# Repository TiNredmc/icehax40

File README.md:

# iCEHAX40
iCEHAX40 - iCE40LP1K-CM36 based FPGA breakout dev board https://oshpark.com/shared_projects/n9XXjf2W

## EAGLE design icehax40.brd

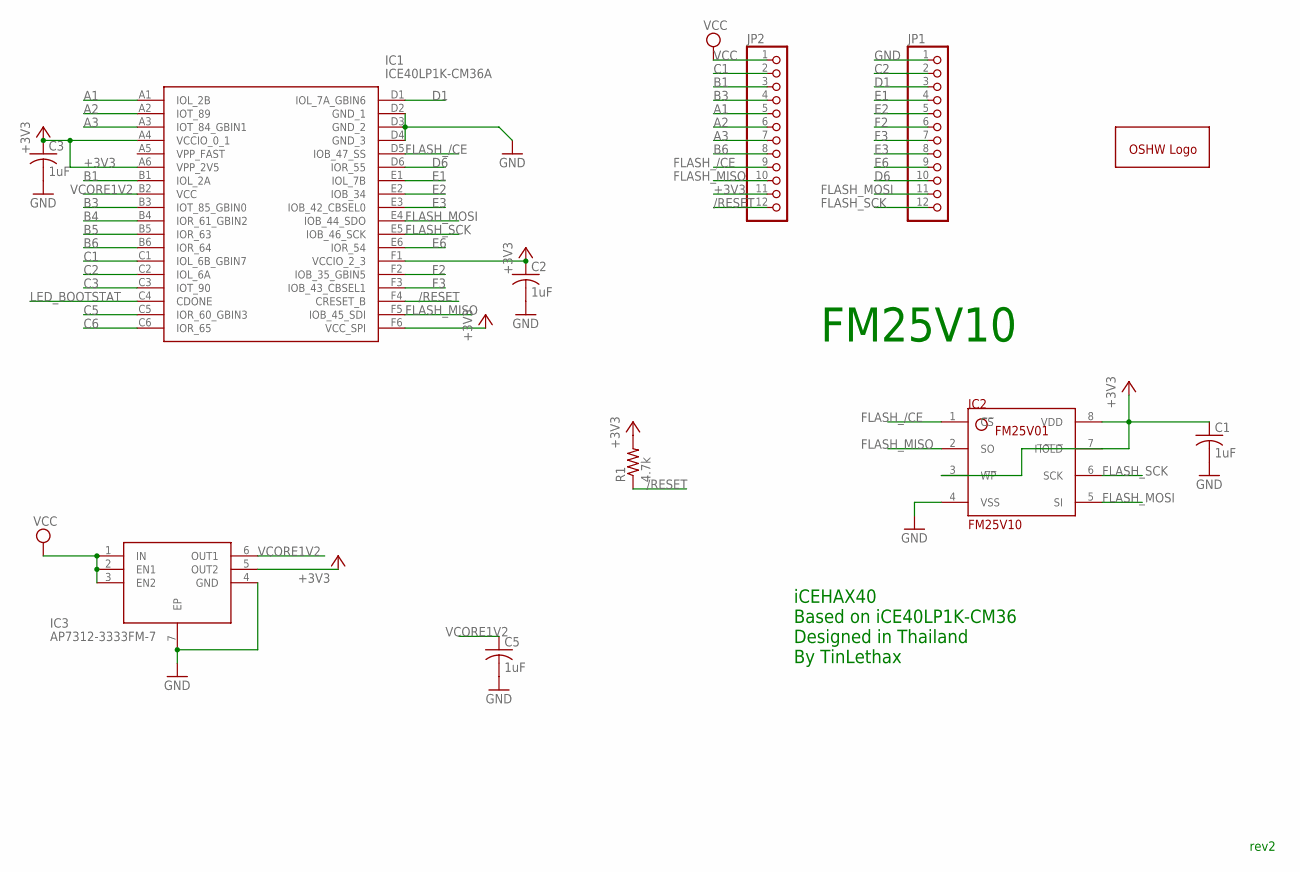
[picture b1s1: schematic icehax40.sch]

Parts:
C1, C2, C3, C5: 1uF; C0603
GOLD_ORB_SM1: OSHWLOGOLOGO5MM; OSHW_5MM
IC1: ICE40LP1K-CM36A; BGA36C40P6X6_250X250X100
IC2: FM25V10; SOIC127P601X172-8N
IC3: AP7312-3333FM-7; SON50P201X181X60-7N
JP1, JP2: PINHD-1X12; 1X12
R1: 4.7k; R0603

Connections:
+3V3: C1.1, C2.1, C3.1, IC1.A4 (VCCIO_0_1), IC1.A6 (VPP_2V5), IC1.F1 (VCCIO_2_3), IC1.F6 (VCC_SPI), IC2.3 (W̅P̅), IC2.7 (H̅O̅L̅D̅), IC2.8 (VDD), IC3.5 (OUT2), JP2.11, R1.2
/RESET: IC1.F4 (CRESET_B), JP2.12, R1.1
A1: IC1.A1 (IOL_2B), JP2.5
A2: IC1.A2 (IOT_89), JP2.6
A3: IC1.A3 (IOT_84_GBIN1), JP2.7
B1: IC1.B1 (IOL_2A), JP2.3
B3: IC1.B3 (IOT_85_GBIN0), JP2.4
B4: IC1.B4 (IOR_61_GBIN2)
B5: IC1.B5 (IOR_63)
B6: IC1.B6 (IOR_64), JP2.8
C1: IC1.C1 (IOL_6B_GBIN7), JP2.2
C2: IC1.C2 (IOL_6A), JP1.2
C3: IC1.C3 (IOT_90)
C5: IC1.C5 (IOR_60_GBIN3)
C6: IC1.C6 (IOR_65)
D1: IC1.D1 (IOL_7A_GBIN6), JP1.3
D6: IC1.D6 (IOR_55), JP1.10
E1: IC1.E1 (IOL_7B), JP1.4
E2: IC1.E2 (IOB_34), JP1.5
E3: IC1.E3 (IOB_42_CBSEL0), JP1.8
E6: IC1.E6 (IOR_54), JP1.9
F2: IC1.F2 (IOB_35_GBIN5), JP1.6
F3: IC1.F3 (IOB_43_CBSEL1), JP1.7
FLASH_/CE: IC1.D5 (IOB_47_SS), IC2.1 (C̅S̅), JP2.9
FLASH_MISO: IC1.F5 (IOB_45_SDI), IC2.2 (SO), JP2.10
FLASH_MOSI: IC1.E4 (IOB_44_SDO), IC2.5 (SI), JP1.11
FLASH_SCK: IC1.E5 (IOB_46_SCK), IC2.6 (SCK), JP1.12
GND: C1.2, C2.2, C3.2, C5.2, IC1.D2 (GND_1), IC1.D3 (GND_2), IC1.D4 (GND_3), IC2.4 (VSS), IC3.4 (GND), IC3.7 (EP), JP1.1
LED_BOOTSTAT: IC1.C4 (CDONE)
VCC: IC3.1 (IN), IC3.2 (EN1), IC3.3 (EN2), JP2.1
VCORE1V2: C5.1, IC1.B2 (VCC), IC3.6 (OUT1)

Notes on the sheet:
iCEHAX40 Based on iCE40LP1K-CM36 Designed in Thailand By TinLethax
FM25V10
rev2

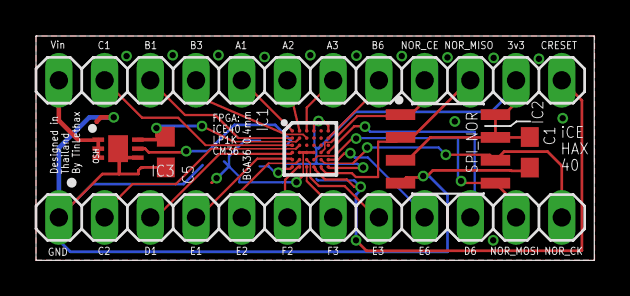
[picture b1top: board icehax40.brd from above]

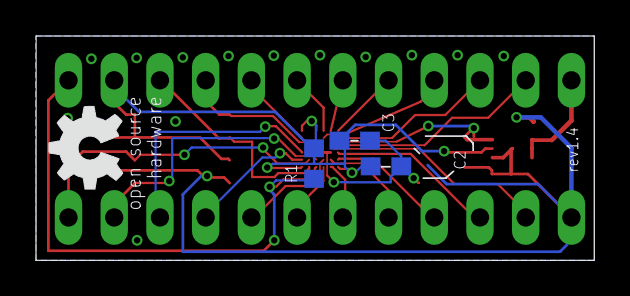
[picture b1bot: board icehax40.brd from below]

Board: 2 copper layers, 31.0 x 12.5 mm, 11 parts (4 on the bottom side), 25 nets.

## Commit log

2022-04-24 Schematic and Board file
2022-05-08 Added image of iCEHAX40
2022-05-08 Added images
2022-05-08 added OSHpark link
